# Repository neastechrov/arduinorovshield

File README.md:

# Arduino ROV Shield V1.0
This project includes schema and board files of Arduino ROV Shield V1.0.

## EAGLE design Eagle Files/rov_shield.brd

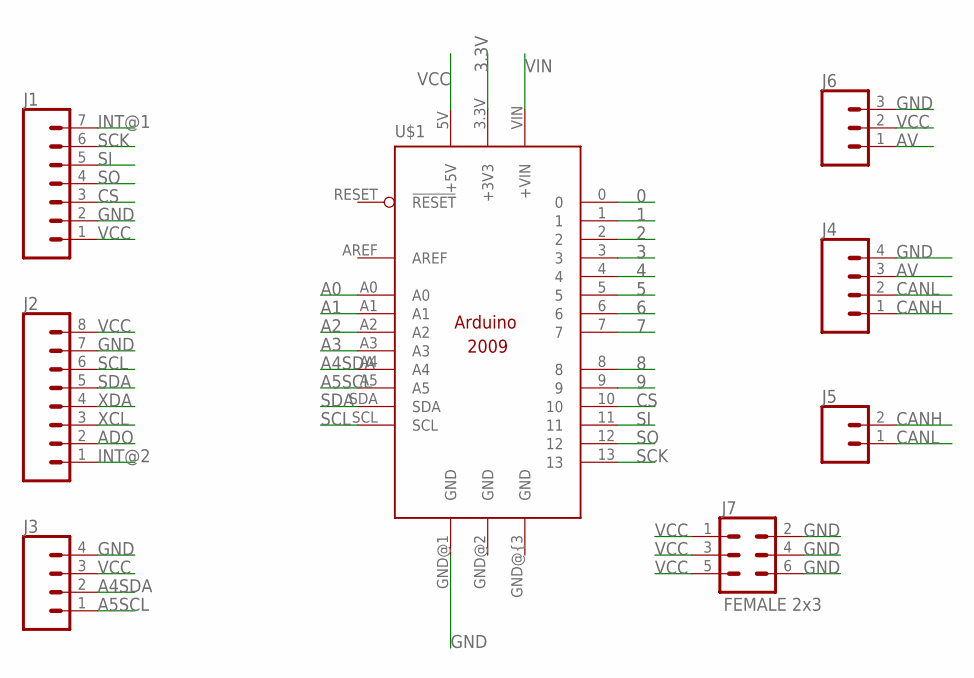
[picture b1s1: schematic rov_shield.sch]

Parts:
J1: CONN_07; 1X07
J2: CONN_08"; 1X08
J3, J4: CONN_04; 1X04
J5: CONN_02; 1X02
J6: CONN_03; 1X03
J7: FEMALE 2x3; 2X3
U$1: ELYAPıMıUNO; ELYAPıNıMUNO

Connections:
0: U$1.0
1: U$1.1
2: U$1.2
3: U$1.3
3.3V: U$1.3.3V (+3V3)
4: U$1.4
5: U$1.5
6: U$1.6
7: U$1.7
8: U$1.8
9: U$1.9
A0: U$1.A0
A1: U$1.A1
A2: U$1.A2
A3: U$1.A3
A4SDA: J3.2, U$1.A4
A5SCL: J3.1, U$1.A5
ADO: J2.2
AV: J4.3, J6.1
CANH: J4.1, J5.2
CANL: J4.2, J5.1
CS: J1.3, U$1.10
GND: J1.2, J2.7, J3.4, J4.4, J6.3, J7.2, J7.4, J7.6, U$1.GND@1 (GND), U$1.GND@2 (GND), U$1.GND@{3 (GND)
INT@1: J1.7
INT@2: J2.1
SCK: J1.6, U$1.13
SCL: J2.6, U$1.SCL
SDA: J2.5, U$1.SDA
SI: J1.5, U$1.11
SO: J1.4, U$1.12
VCC: J1.1, J2.8, J3.3, J6.2, J7.1, J7.3, J7.5, U$1.5V (+5V)
VIN: U$1.VIN (+VIN)
XCL: J2.3
XDA: J2.4

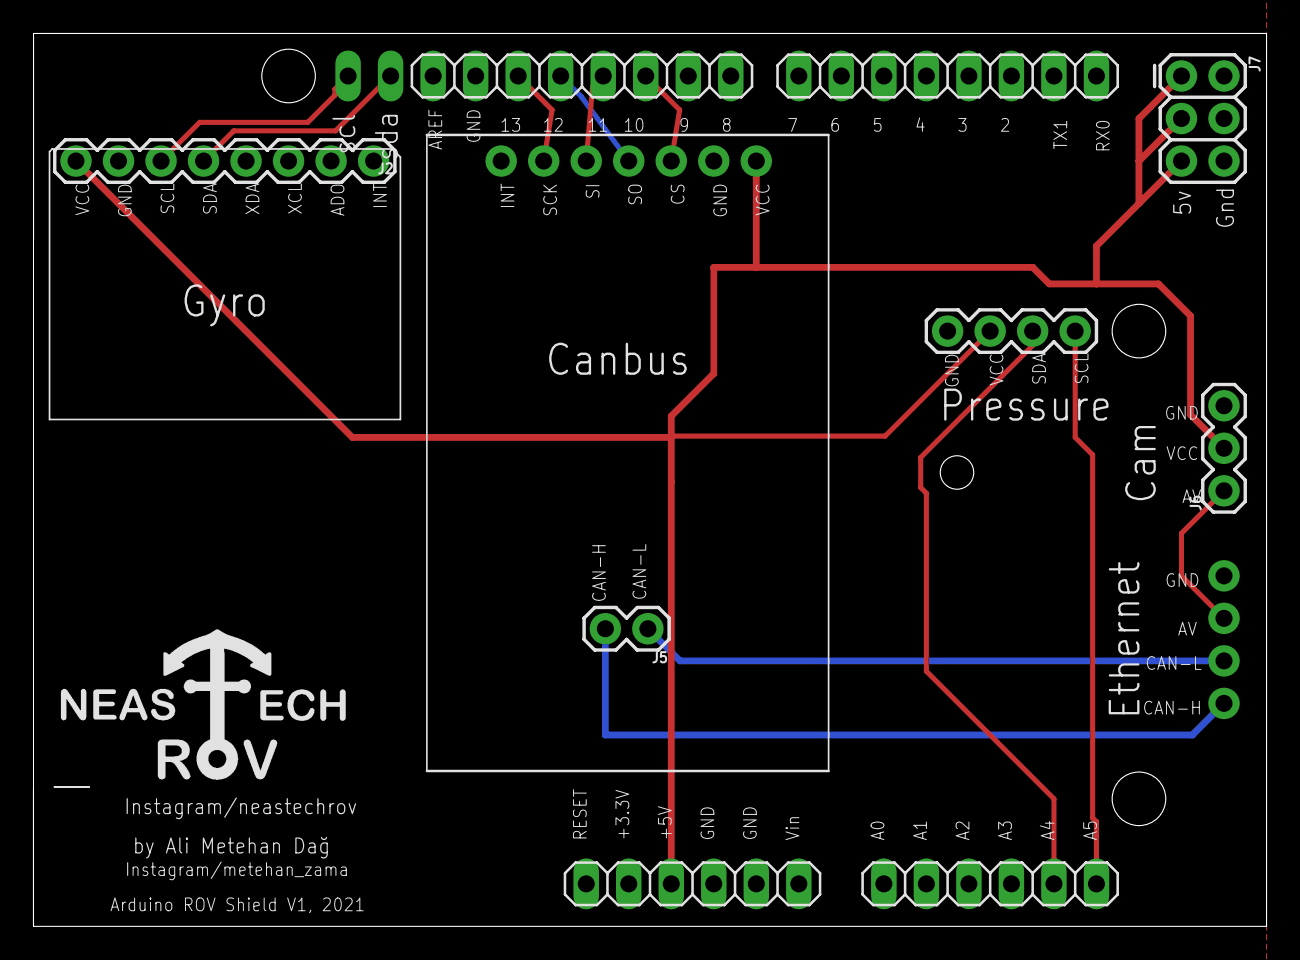
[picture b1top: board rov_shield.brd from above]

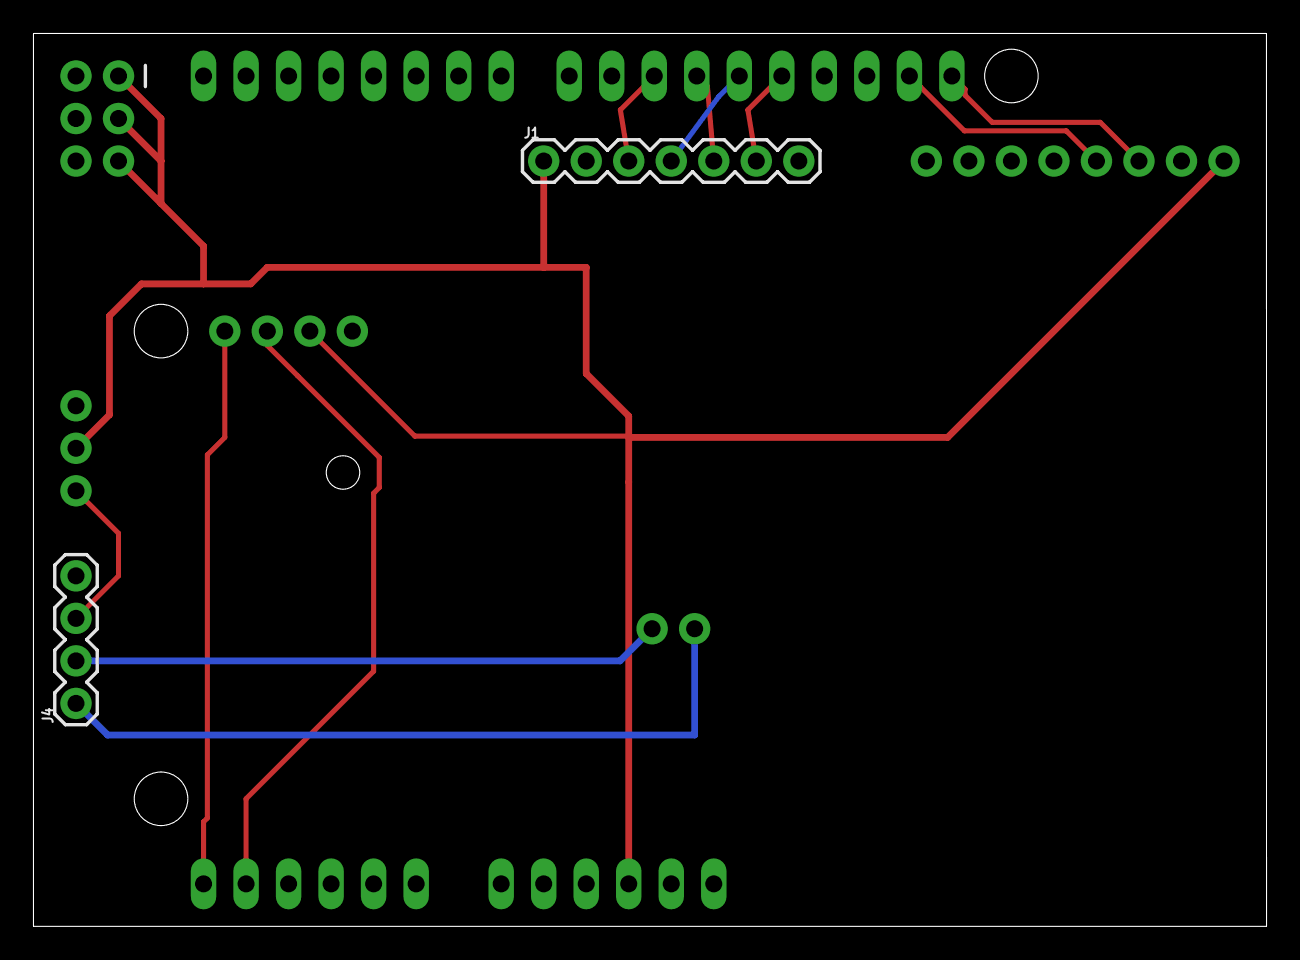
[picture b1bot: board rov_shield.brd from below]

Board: 2 copper layers, 73.7 x 53.3 mm, 8 parts (2 on the bottom side), 13 nets.

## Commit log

2021-05-17 Create a
2021-05-17 Create rov_shield

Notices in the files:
parts and their libraries:
SparkFun-Connectors: Licensing: Creative Commons ShareAlike 4.0 International - https://creativecommons.org/licenses/by-sa/4.0
